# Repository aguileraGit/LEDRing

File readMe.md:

## Update
As best as I can remember, the mold needs to be solid. The silicon-ish material didn't stick well. And apparently I've decided to add a motor driver. I think the PCB is all working (v1.2). I really want to change out the LEDs so they're cheaper.

## READ ME
LED Ring (needs a better name) is an Arduino based platform. It contains a ring of LEDs, accelerometer, Atmel 328p, FTDI, USB (IP68), and debug LED. In the future the device will be encased in silicon-ish type material making the device IP68. Yes, you'll be able to dunk it in water.

## Hardware
A few minor updates need to be done to the HW. Mainly a capacitor to keep the FTDI from resetting and preventing uploads from Arduino IDE. I think there's a capacitor that needs a different footprint.

## Software
Current SW is interruptTest.ino. I really need to create a library to hide a lot of stuff (define DEBUG_LED for example).

Thanks to all who have created libraries and saved me countless hours. Mainly MMA8452 and NeoPixels!

## Mold
Four part mold. Two parts create the mold. The third holds a magnet that interns holds the PCB steady while pouring the silicon. The forth part contains a "nub" to prevent the PCB from wiggling around. This is meant to be printed at 0.1mm resolution. It needs to be glued on to the rest of the mold. The rest of the parts can be printed at 0.2mm.
- Bluesil V-249A/B.
- Hardness: 67A (Fitbit band has a hardness of 60)
- https://www.freemansupply.com/products/mold-making-silicone-rubber/bluestar-addition-cure-silicone-rubber/v-249-mold-making-silicone-rubber-heat-cure
 - Need to upload the 3d mold models.
 - Need to upload print settings.

#### Old references - Might not even be using some of these.
https://github.com/MajenkoLibraries/Average
https://github.com/rocketscream/Low-Power
https://github.com/adafruit/Adafruit_NeoPixel
https://github.com/akupila/Arduino-MMA8452

#### Or these
http://www.engblaze.com/hush-little-microprocessor-avr-and-arduino-sleep-mode-basics/
http://rubenlaguna.com/wp/2008/10/15/arduino-sleep-mode-waking-up-when-receiving-data-on-the-usart/
https://www.arduino.cc/en/Tutorial/SerialEvent
http://donalmorrissey.blogspot.com/2011/11/sleeping-arduino-part-4-wake-up-via.html

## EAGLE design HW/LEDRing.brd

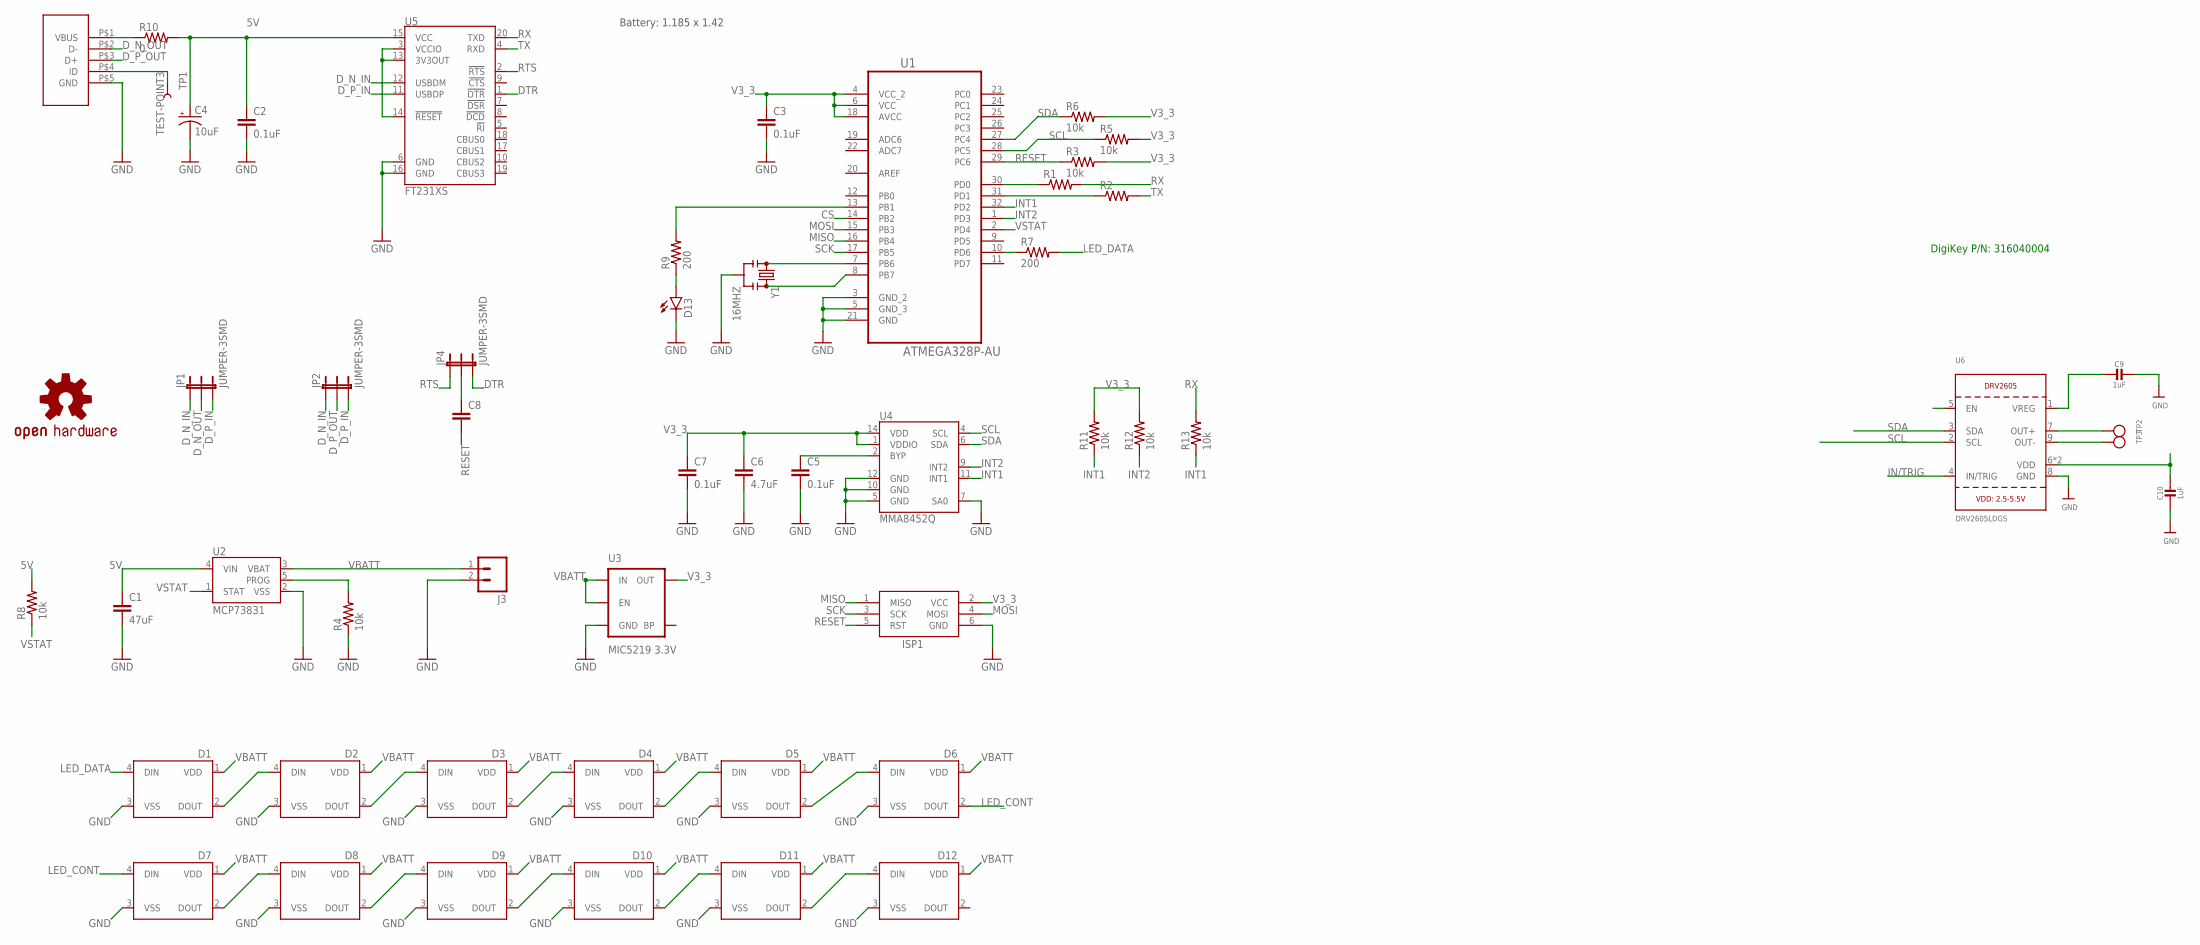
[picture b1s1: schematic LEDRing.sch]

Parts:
C1: 47uF; 0603-CAP
C2, C3, C5, C7: 0.1uF; 0603-CAP
C4: 10uF; 0603-POL
C6: 4.7uF; 0603-CAP
C8: CAP0603-CAP; 0603-CAP
C9, C10: 1uF; 0805-NO
D1, D2, D3, D4, D5, D6, D7, D8, D9, D10, D11, D12: WS2812B
D13: LED0603; LED-0603
ISP1: AVRISP-BOX
J3: M02PTH; 1X02
JP1, JP2, JP4: JUMPER-3SMD; SJ_3
LOGO1: OSHW-LOGOMINI; OSHW-LOGO-MINI
R1, R2: RESISTOR0603-RES; 0603-RES
R3, R4, R5, R6, R8, R11, R12, R13: 10k; 0603-RES
R7, R9: 200; 0603-RES
R10: 0; 0603-RES
TP1: TEST-POINT3; PAD.03X.03
TP2, TP3: TESTPOINTPAD2MM; TESTPOINT_PAD_2MM
U1: ATMEGA328P-AU; QFP80P900X900X120-32N
U2: MCP73831; SOT23-5
U3: MIC5219 3.3V; SOT23-5
U4: MMA8452Q; QFN-16_0.5MM
U5: FT231XS; SSOP20_L
U6: DRV2605LDGS; PSOP10
U$1: TE_USB_A121025CT
Y1: 16MHZ; RESONATOR-SMD

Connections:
5V: C1.1, C2.1, C4.A (+), R8.2, R10.2, U2.4 (VIN), U5.15 (VCC)
CS: U1.14 (PB2)
DTR: JP4.3, U5.1 (!DTR)
D_N_IN: JP1.1, JP2.1, U5.12 (USBDM)
D_N_OUT: JP1.2, U$1.P$2 (D-)
D_P_IN: JP1.3, JP2.3, U5.11 (USBDP)
D_P_OUT: JP2.2, U$1.P$3 (D+)
GND: C1.2, C2.2, C3.2, C4.K (-), C5.2, C6.2, C7.2, C9.1, C10.2, D1.3 (VSS), D2.3 (VSS), D3.3 (VSS), D4.3 (VSS), D5.3 (VSS), D6.3 (VSS), D7.3 (VSS), D8.3 (VSS), D9.3 (VSS), D10.3 (VSS), D11.3 (VSS), D12.3 (VSS), D13.C, ISP1.6 (GND), J3.2, R4.1, U1.3 (GND_2), U1.5 (GND_3), U1.21 (GND), U2.2 (VSS), U3.2 (GND), U4.5 (GND), U4.7 (SA0), U4.10 (GND), U4.12 (GND), U5.6 (GND), U5.16 (GND), U6.8 (GND), U$1.P$5 (GND), Y1.2
IN/TRIG: U6.4 (IN/TRIG)
INT1: R11.1, R13.1, U1.32 (PD2), U4.11 (INT1)
INT2: R12.1, U1.1 (PD3), U4.9 (INT2)
LED_CONT: D6.2 (DOUT), D7.4 (DIN)
LED_DATA: D1.4 (DIN), R7.2
MISO: ISP1.1 (MISO), U1.16 (PB4)
MOSI: ISP1.4 (MOSI), U1.15 (PB3)
unnamed: R1.1, U1.30 (PD0)
unnamed: R2.1, U1.31 (PD1)
unnamed: C5.1, U4.2 (BYP)
unnamed: R10.1, U$1.P$1 (VBUS)
unnamed: U5.3 (VCCIO), U5.13 (3V3OUT), U5.14 (!RESET)
unnamed: U1.8 (PB7), Y1.3
unnamed: U1.7 (PB6), Y1.1
unnamed: R4.2, U2.5 (PROG)
unnamed: R7.1, U1.10 (PD6)
unnamed: D1.2 (DOUT), D2.4 (DIN)
unnamed: D2.2 (DOUT), D3.4 (DIN)
unnamed: D3.2 (DOUT), D4.4 (DIN)
unnamed: D4.2 (DOUT), D5.4 (DIN)
unnamed: D5.2 (DOUT), D6.4 (DIN)
unnamed: D7.2 (DOUT), D8.4 (DIN)
unnamed: D8.2 (DOUT), D9.4 (DIN)
unnamed: D9.2 (DOUT), D10.4 (DIN)
unnamed: D10.2 (DOUT), D11.4 (DIN)
unnamed: D11.2 (DOUT), D12.4 (DIN)
unnamed: C9.2, U6.1 (VREG)
unnamed: R9.2, U1.13 (PB1)
unnamed: D13.A, R9.1
unnamed: TP1.P$1, U$1.P$4 (ID)
unnamed: C10.1, U6.6 (VDD), U6.10 (VDD)
OUT+: TP2.P$1, U6.7 (OUT+)
OUT-: TP3.P$1, U6.9 (OUT-)
RESET: C8.2, ISP1.5 (RST), R3.1, U1.29 (PC6)
RTS: JP4.1, U5.2 (!RTS)
RTS_OR_DTR: C8.1, JP4.2
RX: R1.2, R13.2, U5.20 (TXD)
SCK: ISP1.3 (SCK), U1.17 (PB5)
SCL: R5.1, U1.28 (PC5), U4.4 (SCL), U6.2 (SCL)
SDA: R6.1, U1.27 (PC4), U4.6 (SDA), U6.3 (SDA)
TX: R2.2, U5.4 (RXD)
V3_3: C3.1, C6.1, C7.1, ISP1.2 (VCC), R3.2, R5.2, R6.2, R11.2, R12.2, U1.4 (VCC_2), U1.6 (VCC), U1.18 (AVCC), U3.5 (OUT), U4.1 (VDDIO), U4.14 (VDD)
VBATT: D1.1 (VDD), D2.1 (VDD), D3.1 (VDD), D4.1 (VDD), D5.1 (VDD), D6.1 (VDD), D7.1 (VDD), D8.1 (VDD), D9.1 (VDD), D10.1 (VDD), D11.1 (VDD), D12.1 (VDD), J3.1, U2.3 (VBAT), U3.1 (IN), U3.3 (EN)
VSTAT: R8.1, U1.2 (PD4), U2.1 (STAT)

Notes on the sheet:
Battery: 1.185 x 1.42
DigiKey P/N: 316040004

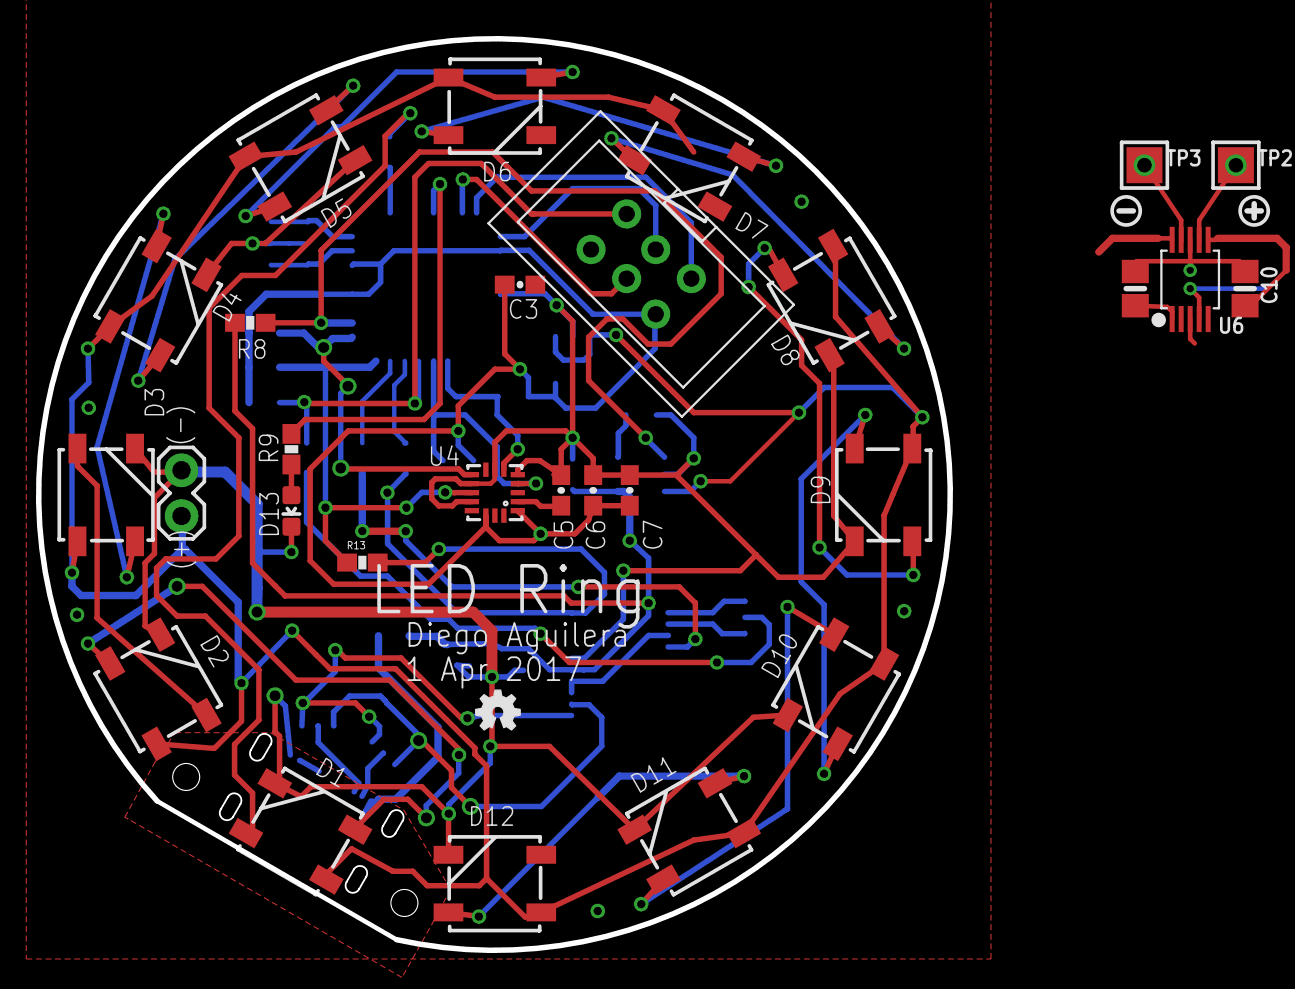
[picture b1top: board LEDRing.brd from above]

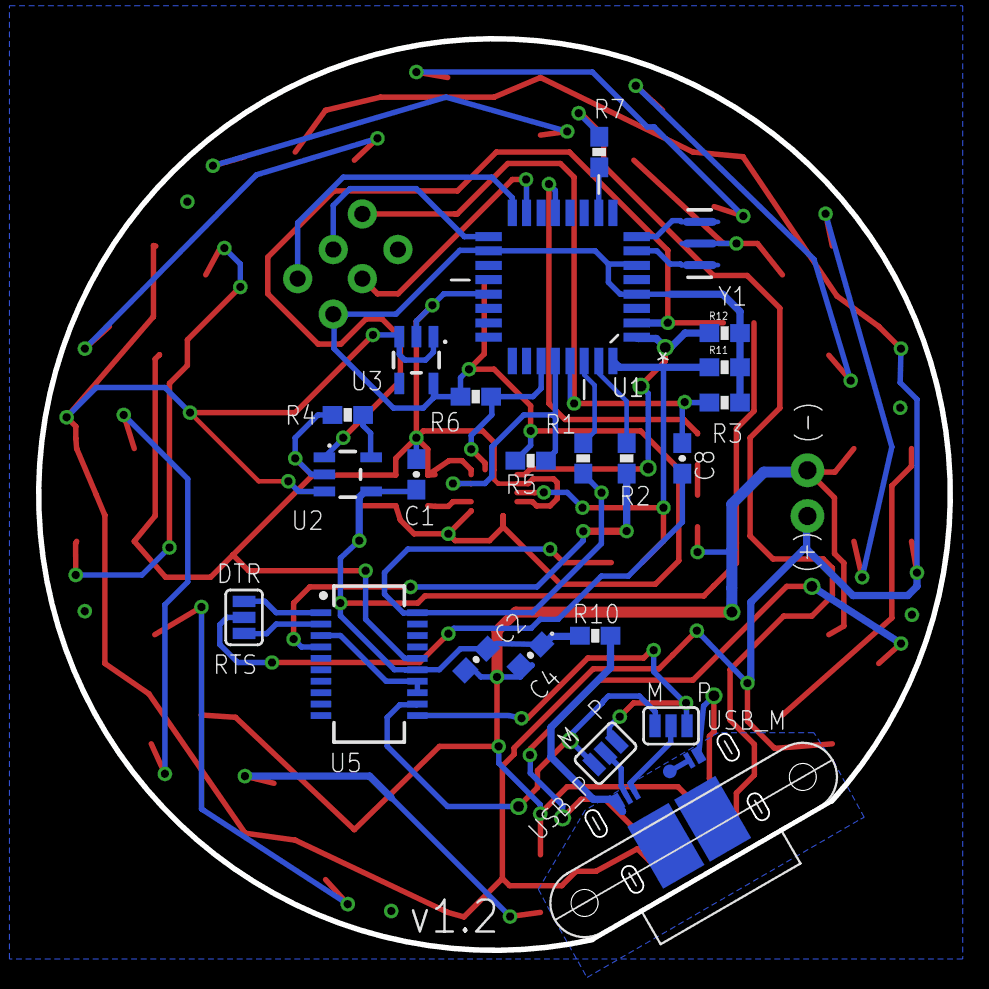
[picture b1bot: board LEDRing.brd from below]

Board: 2 copper layers, 50.6 x 50.6 mm, 55 parts (24 on the bottom side), 50 nets.

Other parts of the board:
U$5: SYMBOL_PLUS
U$13: SYMBOL_MINUS

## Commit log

2016-10-12 Init commit
2016-10-14 Added accelerometer Added power Added LEDs
2016-10-20 More updates to layout
2016-10-20 Added script to calculate LED positions
2016-10-20 Updated schematics
2016-10-27 More routing done
2016-11-10 Added USB connector. Needs to be finished. Added python script to help with USB connector layout
2016-11-15 Moved USB connector
2016-11-16 Removed most USB footprint errors
2016-11-16 Moved LEDs so USB fits
2016-11-16 Started tieing LED VSS to GND
2016-11-17 Finished layout. Need to fix text
2016-11-18 Sent board to be made
2016-12-03 Modified folder structure Added Sparkfun and n0m1 libraries Modified library to add tap and double taps! UNFINISHED
2016-12-16 Updated schematics.
2016-12-16 Adding ignore file.
2016-12-16 Removed some files.
2016-12-19 Adding PCB changes for next version.
2017-01-18 Updated to version 1.1.
2017-02-06 Found error for USB part. Fixed. Still need to move usb to original spot.
2017-02-06 Adding LED Heart for the time being.
2017-03-02 Moved USB connector.
2017-03-08 Added 0.1uF and 1000uF capacitors. (Need to finish) Added values for components.
2017-03-09 Added a few sample programs.
2017-03-22 Ready for next version? Should probably double check.
2017-03-30 Updated Version
2017-06-08 Uploaded image of schematics
2017-06-09 Adding code examples.
2017-06-12 Added interruptTest
2017-06-13 Quick update before bed.
2017-06-16 Added sleep to interruptTest.ino
2018-07-07 Updating all files. I've started adding a motor driver (vibration motor).

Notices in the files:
parts and their libraries:
SparkFun-Capacitors: Licensing: Creative Commons ShareAlike 4.0 International - https://creativecommons.org/licenses/by-sa/4.0
microbuilder: This work is placed in the public domain, and may be freely used for commercial and non-commercial work with the following conditions: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
